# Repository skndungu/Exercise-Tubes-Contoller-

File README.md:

# Exercise-Tubes-Contoller
Controller for exercise tubes 

# Exercise Tubes Contoller 3 Speed Levels

Test codes for solenoids driven via io expander and the arduino

The Code is used to test the PCB board and connections with the solenoids, it put on/off the solenoids at intervals of one sec

PCF8574 GPIO Extender
---
i2c addresses, the table below is used to assign the addresses

Programming
---
- Download the codes from the codes from the ⬇️ on the code section, you will get a folder with the name 📁 `Exercise-Tubes-Contoller--master`
- Extract the content of the zipped file, you will get the firmware codes and another folder with the name 📁 `libs` extract the content from the folder and paste it on your 📂 `documents/Arduino/library/` directory to add the lib used in this case
- Compile and run codes
- Upload to the dev board and test out your codes!

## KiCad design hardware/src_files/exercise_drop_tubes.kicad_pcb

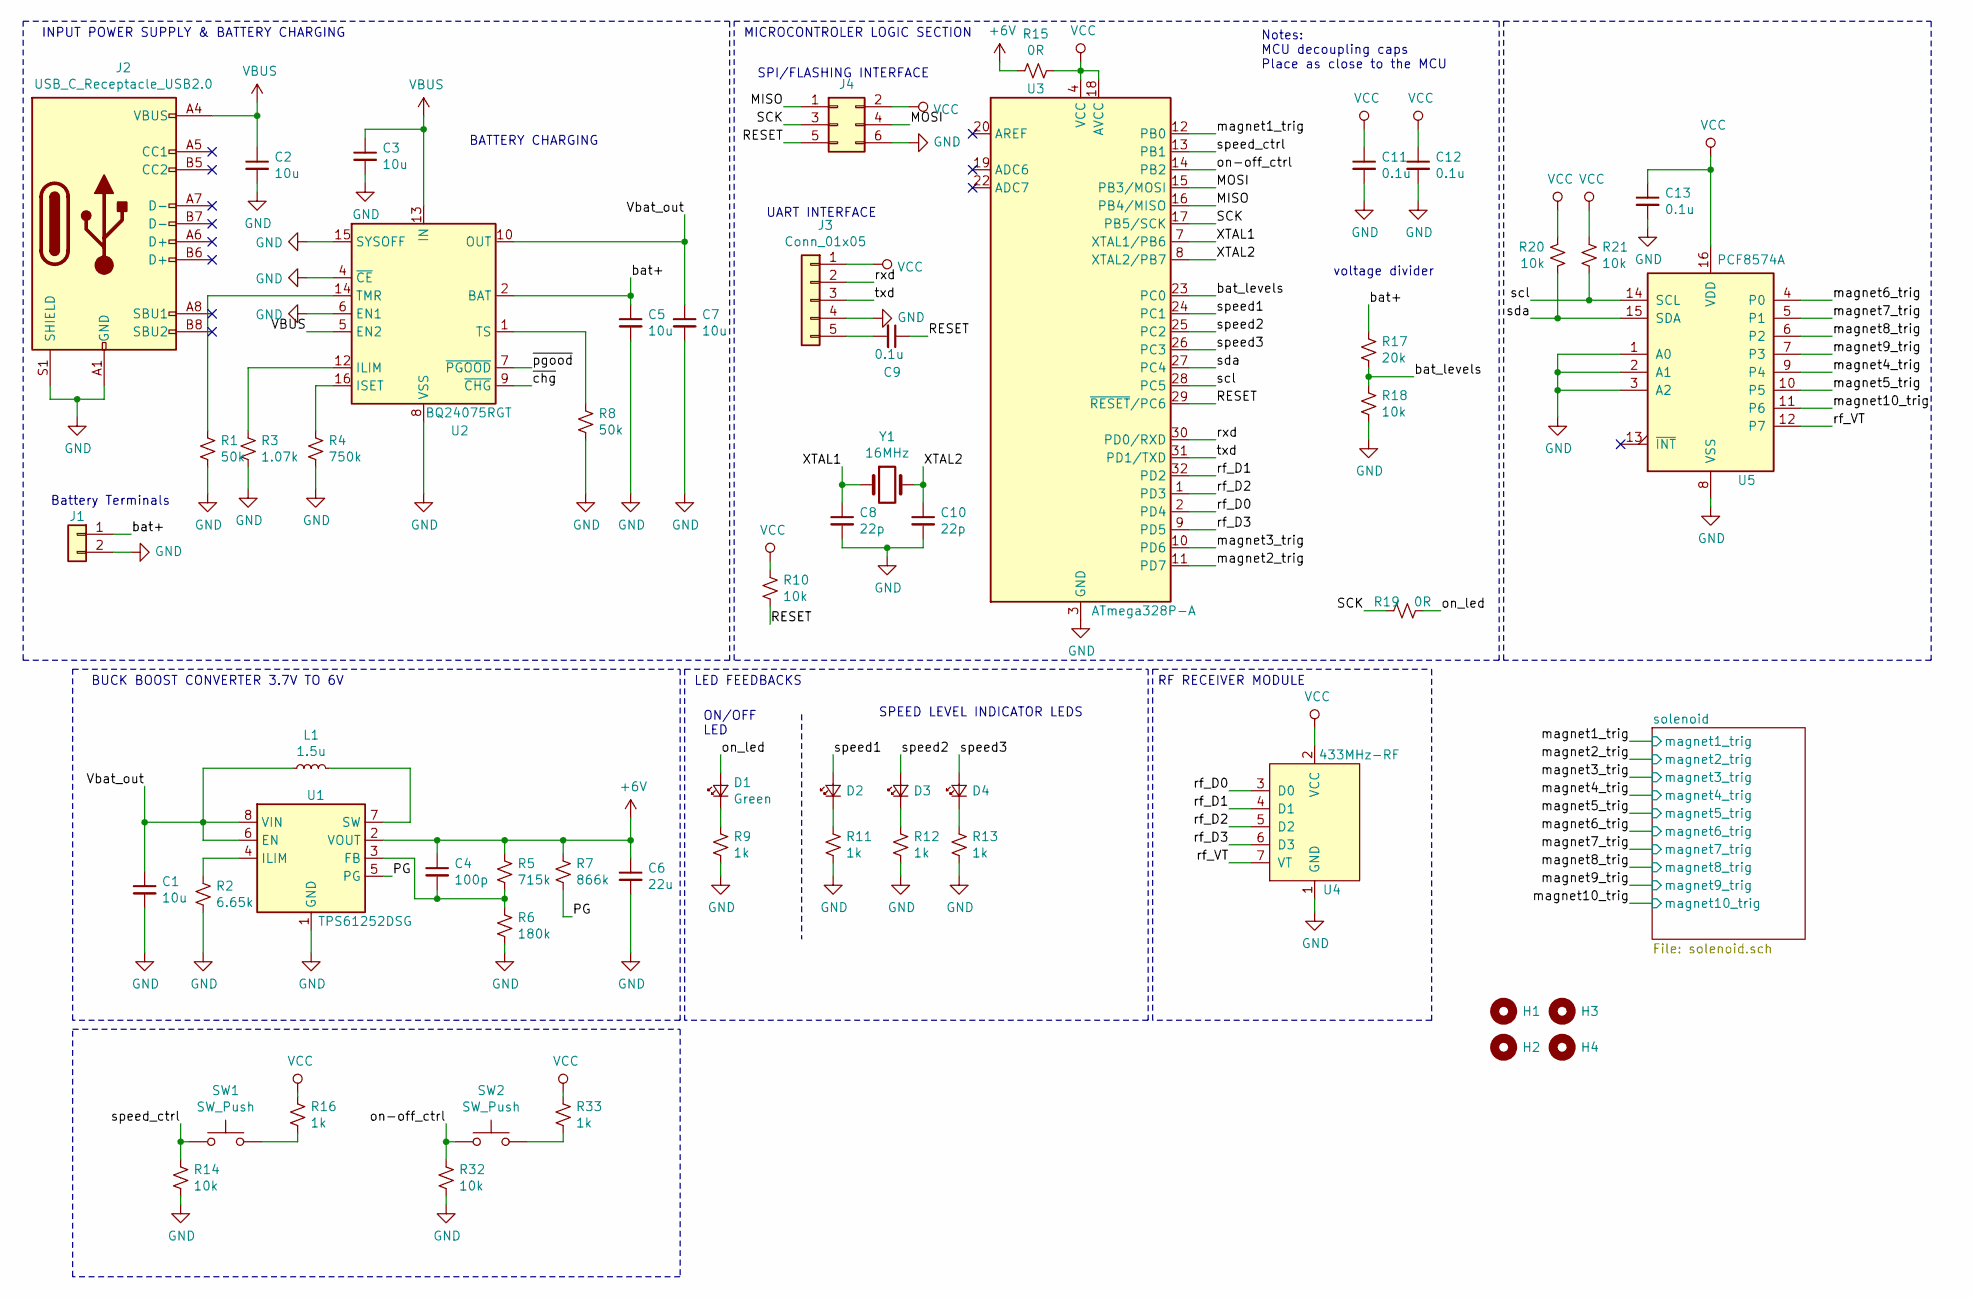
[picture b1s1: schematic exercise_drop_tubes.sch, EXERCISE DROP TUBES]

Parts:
C1, C2, C3, C5, C7: 10u; C_0603_1608Metric
C4: 100p; C_0603_1608Metric
C6: 22u; C_0603_1608Metric
C8, C10: 22p; C_0603_1608Metric
C9, C11, C12, C13: 0.1u; C_0603_1608Metric
D1: Green; LED_Rectangular_W3.0mm_H2.0mm
D2, D3, D4: LED_Small; LED_Rectangular_W3.0mm_H2.0mm
H1, H2, H3, H4: MountingHole; MountingHole_3.2mm_M3
J1: Conn_01x02; JST_XH_S2B-XH-A_1x02_P2.50mm_Horizontal
J2: USB_C_Receptacle_USB2.0; USB_C_Receptacle_Amphenol_12401548E4-2A
J3: Conn_01x05; PinHeader_1x05_P2.54mm_Vertical
J4: Conn_02x03_Odd_Even; PinHeader_2x03_P2.54mm_Vertical
L1: 1.5u; YSPI1050-xxx
R1, R8: 50k; R_0603_1608Metric
R2: 6.65k; R_0603_1608Metric
R3: 1.07k; R_0603_1608Metric
R4: 750k; R_0603_1608Metric
R5: 715k; R_0603_1608Metric
R6: 180k; R_0603_1608Metric
R7: 866k; R_0603_1608Metric
R9, R11, R12, R13, R16, R33: 1k; R_0603_1608Metric
R10, R14, R18, R20, R21, R32: 10k; R_0603_1608Metric
R15, R19: 0R; R_0603_1608Metric
R17: 20k; R_0603_1608Metric
SW1, SW2: SW_Push; UK-B0206-G8-160
U1: TPS61252DSG; WSON-8-1EP_2x2mm_P0.5mm_EP0.9x1.6mm
U2: BQ24075RGT; VQFN-16-1EP_3x3mm_P0.5mm_EP1.68x1.68mm_ThermalVias
U3: ATmega328P-A; TQFP-32_7x7mm_P0.8mm
U4: 433MHz-RF; RF-RX-433; Mfr# RX480E-4
U5: PCF8574A; SOIC-16W_7.5x10.3mm_P1.27mm
Y1: 16MHz; Crystal_SMD_Abracon_ABM8G-4Pin_3.2x2.5mm

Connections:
+6V: C4.1, C6.1, R5.1, R7.1, R15.2, U1.2 (VOUT); also elsewhere on the board
/MISO: J4.1, U3.16 (PB4/MISO)
/MOSI: J4.4, U3.15 (PB3/MOSI)
/PG: R7.2, U1.5 (PG)
/RESET: C9.1, J4.5, R10.1, U3.29 (~RESET~/PC6)
/SCK: J4.3, R19.2, U3.17 (PB5/SCK)
/Vbat_out: C1.1, C7.1, L1.1, U1.6 (EN), U1.8 (VIN), U2.10 (OUT), U2.11 (OUT)
/XTAL1: C8.1, U3.7 (XTAL1/PB6), Y1.1
/XTAL2: C10.1, U3.8 (XTAL2/PB7), Y1.3
/bat+: C5.1, J1.1, R17.1, U2.2 (BAT), U2.3 (BAT)
/bat_levels: R17.2, R18.1, U3.23 (PC0)
/magnet1_trig: U3.12 (PB0); also elsewhere on the board
/magnet2_trig: U3.11 (PD7); also elsewhere on the board
/magnet3_trig: U3.10 (PD6); also elsewhere on the board
/magnet4_trig: U5.9 (P4); also elsewhere on the board
/magnet5_trig: U5.10 (P5); also elsewhere on the board
/magnet6_trig: U5.4 (P0); also elsewhere on the board
/magnet7_trig: U5.5 (P1); also elsewhere on the board
/magnet8_trig: U5.6 (P2); also elsewhere on the board
/magnet9_trig: U5.7 (P3); also elsewhere on the board
/magnet10_trig: U5.11 (P6); also elsewhere on the board
/on-off_ctrl: R32.1, SW2.1, U3.14 (PB2)
/on_led: D1.2 (A), R19.1
/rf_D0: U3.2 (PD4), U4.3 (D0)
/rf_D1: U3.32 (PD2), U4.4 (D1)
/rf_D2: U3.1 (PD3), U4.5 (D2)
/rf_D3: U3.9 (PD5), U4.6 (D3)
/rf_VT: U4.7 (VT), U5.12 (P7)
/rxd: J3.2, U3.30 (PD0/RXD)
/scl: R21.2, U3.28 (PC5), U5.14 (SCL)
/sda: R20.2, U3.27 (PC4), U5.15 (SDA)
/speed1: D2.2 (A), U3.24 (PC1)
/speed2: D3.2 (A), U3.25 (PC2)
/speed3: D4.2 (A), U3.26 (PC3)
/speed_ctrl: R14.1, SW1.1, U3.13 (PB1)
/txd: J3.3, U3.31 (PD1/TXD)
GND: C1.2, C2.2, C3.2, C5.2, C6.2, C7.2, C8.2, C10.2, C11.2, C12.2, C13.2, J1.2, J2.A1 (GND), J2.A12 (GND), J2.B1 (GND), J2.B12 (GND), J2.S1 (SHIELD), J3.4, J4.6, R1.2, R2.2, R3.2, R4.2, R6.2, R8.2, R9.2, R11.2, R12.2, R13.2, R14.2, R18.2, R32.2, U1.1 (GND), U1.9 (GND), U2.4 (~CE), U2.6 (EN1), U2.8 (VSS), U2.15 (SYSOFF), U2.17 (VSS), U3.3 (GND), U3.5 (GND), U3.21 (GND), U4.1 (GND), U5.1 (A0), U5.2 (A1), U5.3 (A2), U5.8 (VSS); also elsewhere on the board
unnamed: C4.2, R5.2, R6.1, U1.3 (FB)
unnamed: C9.2, J3.5
unnamed: D1.1 (K), R9.1
unnamed: D2.1 (K), R11.1
unnamed: D3.1 (K), R12.1
unnamed: D4.1 (K), R13.1
unnamed: L1.2, U1.7 (SW)
unnamed: R1.1, U2.14 (TMR)
unnamed: R2.1, U1.4 (ILIM)
unnamed: R3.1, U2.12 (ILIM)
unnamed: R4.1, U2.16 (ISET)
unnamed: R8.1, U2.1 (TS)
unnamed: R16.2, SW1.3
unnamed: R33.2, SW2.3
VBUS: C2.1, C3.1, J2.A4 (VBUS), J2.A9 (VBUS), J2.B4 (VBUS), J2.B9 (VBUS), U2.5 (EN2), U2.13 (IN)
VCC: C11.1, C12.1, C13.1, J3.1, J4.2, R10.2, R15.1, R16.1, R20.1, R21.1, R33.1, U3.4 (VCC), U3.6 (VCC), U3.18 (AVCC), U4.2 (VCC), U5.16 (VDD)

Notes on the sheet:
Notes: MCU decoupling caps Place as close to the MCU
Battery Terminals
voltage divider
INPUT POWER SUPPLY & BATTERY CHARGING
BUCK BOOST CONVERTER 3.7V TO 6V
MICROCONTROLER LOGIC SECTION
UART INTERFACE
SPI/FLASHING INTERFACE
BATTERY CHARGING
ON/OFF LED
SPEED LEVEL INDICATOR LEDS
LED FEEDBACKS
RF RECEIVER MODULE

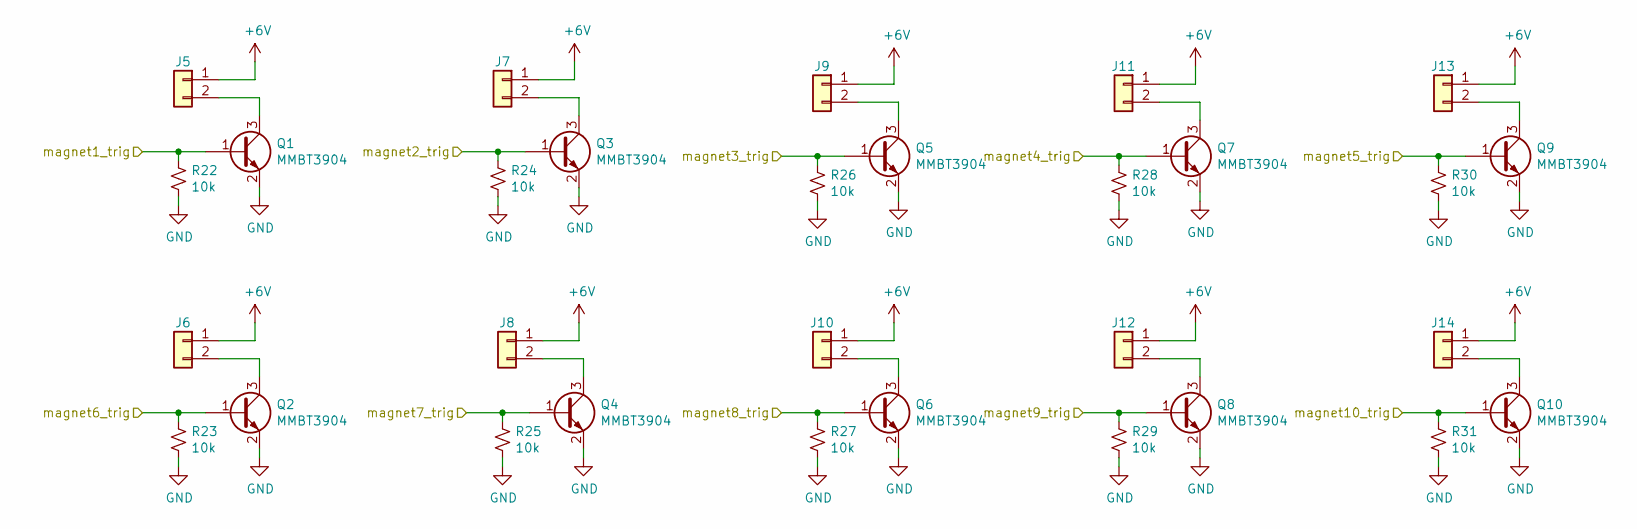
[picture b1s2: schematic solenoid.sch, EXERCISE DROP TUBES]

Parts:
J5, J6, J7, J8, J9, J10, J11, J12, J13, J14: Conn_01x02; JST_XH_S2B-XH-A_1x02_P2.50mm_Horizontal
Q1, Q2, Q3, Q4, Q5, Q6, Q7, Q8, Q9, Q10: MMBT3904; SOT-23
R22, R23, R24, R25, R26, R27, R28, R29, R30, R31: 10k; R_0603_1608Metric

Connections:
+6V: J5.1, J6.1, J7.1, J8.1, J9.1, J10.1, J11.1, J12.1, J13.1, J14.1; also elsewhere on the board
/magnet1_trig: Q1.1 (B), R22.1; also elsewhere on the board
/magnet2_trig: Q3.1 (B), R24.1; also elsewhere on the board
/magnet3_trig: Q5.1 (B), R26.1; also elsewhere on the board
/magnet4_trig: Q7.1 (B), R28.1; also elsewhere on the board
/magnet5_trig: Q9.1 (B), R30.1; also elsewhere on the board
/magnet6_trig: Q2.1 (B), R23.1; also elsewhere on the board
/magnet7_trig: Q4.1 (B), R25.1; also elsewhere on the board
/magnet8_trig: Q6.1 (B), R27.1; also elsewhere on the board
/magnet9_trig: Q8.1 (B), R29.1; also elsewhere on the board
/magnet10_trig: Q10.1 (B), R31.1; also elsewhere on the board
GND: Q1.2 (E), Q2.2 (E), Q3.2 (E), Q4.2 (E), Q5.2 (E), Q6.2 (E), Q7.2 (E), Q8.2 (E), Q9.2 (E), Q10.2 (E), R22.2, R23.2, R24.2, R25.2, R26.2, R27.2, R28.2, R29.2, R30.2, R31.2; also elsewhere on the board
unnamed: J5.2, Q1.3 (C)
unnamed: J6.2, Q2.3 (C)
unnamed: J7.2, Q3.3 (C)
unnamed: J8.2, Q4.3 (C)
unnamed: J9.2, Q5.3 (C)
unnamed: J10.2, Q6.3 (C)
unnamed: J11.2, Q7.3 (C)
unnamed: J12.2, Q8.3 (C)
unnamed: J13.2, Q9.3 (C)
unnamed: J14.2, Q10.3 (C)

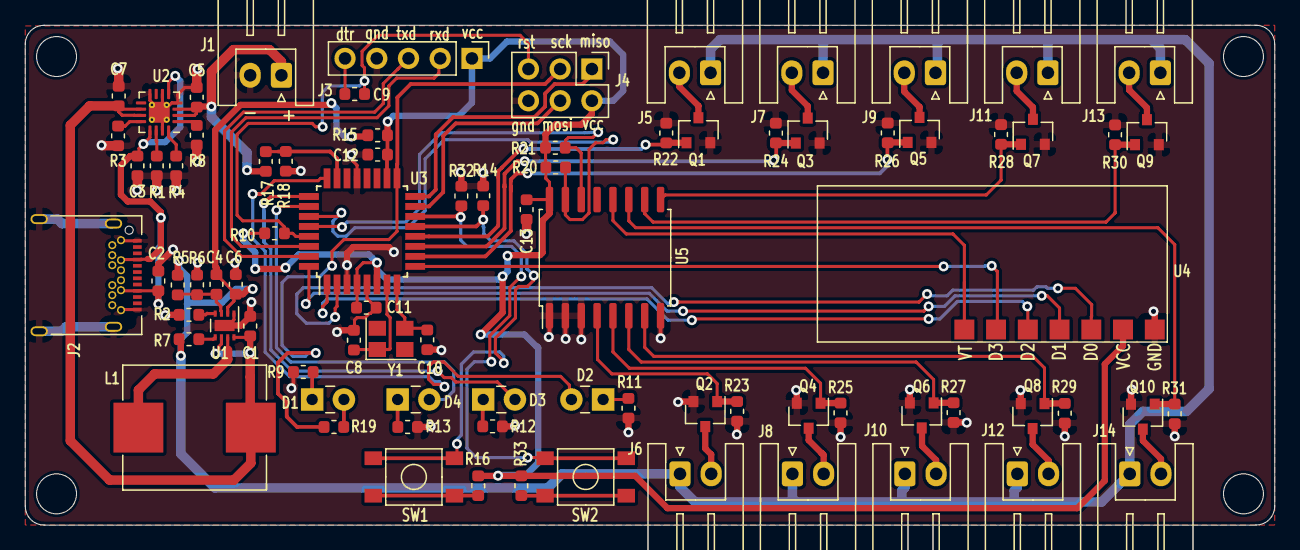
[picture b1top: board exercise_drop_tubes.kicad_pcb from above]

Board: 2 copper layers, 100.0 x 40.0 mm, 87 parts (0 on the bottom side), 63 nets.

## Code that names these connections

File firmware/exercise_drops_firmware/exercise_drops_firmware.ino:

/*
* Title: Exercise Drop Tubes 
*
* Author: Simon Ndungu
*
* Date: 21st Nov 2021
*/
#include "Arduino.h"
#include "PCF8574.h"

/* U5 --> A0,A1,A2 = 0 => address => 0x20 */
/* Set i2c address */ 
// create an object of the PCF8574 
PCF8574 pcf8574_U1(0x20);

#define solenoid1_trig 8
#define solenoid2_trig 7
#define solenoid3_trig 6

#define speed_ctrl_btn 9
#define on_off_ctrl_btn 10

#define bat_level A0

#define speed1_led A1
#define speed2_led A2
#define speed3_led A3
#define status_led 13

#define rf_d0 2
#define rf_d1 3
#define rf_d2 4
#define rf_d3 5

float R1 = 20000;
float R2 = 10000;
float voltage_raw_val = 0.00;
float voltage_out = 0.00;
float battery_voltage = 0.00;
float correction_factor = 0.13;

int random_tube;
int previous_random_tube;
int speed_ctrl_btn_state = 0;
int on_off_ctrl_btn_state = 0;


unsigned long currentMillis=0;
unsigned long previousMillis = 0;
int speed1 = 1000; // value can be changed by buttons
int speed2 = 2000;
int speed3 = 3000; 
int interval; 

bool level1_speed = true;
bool level2_speed = false;
bool level3_speed = false;

int count = 0;



void setup() {
  // put your setup code here, to run once:
	  pcf8574_U1.pinMode(P0, OUTPUT); // solenoid 6
      pcf8574_U1.pinMode(P1, OUTPUT); // solenoid 7
      pcf8574_U1.pinMode(P2, OUTPUT); // solenoid 8
      pcf8574_U1.pinMode(P3, OUTPUT); // solenoid 4
      pcf8574_U1.pinMode(P5, OUTPUT); // solenoid 5
      pcf8574_U1.pinMode(P6, OUTPUT); // solenoid 10
      pcf8574_U1.pinMode(P7, OUTPUT); // RF VT signal

      pinMode(solenoid1_trig, OUTPUT);
      pinMode(solenoid2_trig, OUTPUT);
      pinMode(solenoid3_trig, OUTPUT);

      pinMode(speed1_led, OUTPUT);
      pinMode(speed2_led, OUTPUT);
      pinMode(speed3_led, OUTPUT);
      pinMode(status_led, OUTPUT);

      pinMode(speed_ctrl_btn, INPUT);
      pinMode(on_off_ctrl_btn, INPUT);
      pinMode(bat_level, INPUT);

}

void loop() {
  // put your main code here, to run repeatedly:
   unsigned long currentMillis = millis();

   execute_speed_change();
   
   generate_random_tube(); // executes the tubes

}

void take_reading(){
  voltage_raw_val = analogRead(bat_level);
  speed_ctrl_btn_state = digitalRead(speed_ctrl_btn);
  on_off_ctrl_btn_state = digitalRead(on_off_ctrl_btn);

  Serial.print("Raw Value");
  Serial.println(voltage_raw_val);
}

void check_battery_voltage(){
  take_reading();
  voltage_out = (voltage_raw_val * 5) / 1024; 
  battery_voltage = voltage_out / (R2/(R1+ R2)) - correction_factor;
  Serial.print("Measured Voltage is: ");
  Serial.print(battery_voltage);
  Serial.println("V");
  }


void speed1_led_on(){
   digitalWrite(speed1_led, HIGH);
}
void speed1_led_off(){
  digitalWrite(speed1_led, LOW);
}
void speed2_led_on(){
  digitalWrite(speed2_led, HIGH);
}
void speed2_led_off(){
  digitalWrite(speed2_led, LOW);
}
void speed3_led_on(){
  digitalWrite(speed3_led, HIGH);
}
void speed3_led_off(){
  digitalWrite(speed3_led, LOW);
}

int generate_random_tube(){
   if ((unsigned long )(currentMillis - previousMillis) >= interval) {
      random_tube = random(11);
      Serial.print("Random Number");
      Serial.println(random_tube);
      previousMillis = currentMillis;
      previous_random_tube = random_tube;
   }

   return random_tube;
   trigger_solenoids();
}

void listen_change_speed(){
   if(speed_ctrl_btn_state == 1){
      count +=1;
   }

   if(count == 1){
   	 level1_speed = true;
     level2_speed = false;
     level3_speed = false;
   }

   if(count == 2){
     level1_speed = false;
     level2_speed = true;
     level3_speed = false;
   }

   if(count == 3){
     level1_speed = false;
     level2_speed = false;
     level3_speed = true;
   }

   if(count > 3){
    count = 1; //resets count to 1 if val > 3(reps speed levels)
   }
   
}

void execute_speed_change(){
  listen_change_speed();
  if(level1_speed){
    speed1_led_on();
    speed2_led_off();
    speed3_led_off();
    interval = speed3; // level 1 is the slowest speed 
  }
    if(level2_speed){
    speed1_led_off();
    speed2_led_on();
    speed3_led_off();
    interval = speed2; // level 2 is the medium speed 
  }
    if(level3_speed){
    speed1_led_off();
    speed2_led_off();
    speed3_led_on();
    interval = speed1; // level 1 is the fastest speed 
  }
}

void trigger_solenoids(){
 int tube = generate_random_tube();
 Serial.print("Random Tube Passed is: ");
 Serial.println(tube);
 if(tube == 1){
   digitalWrite(solenoid1_trig, HIGH);
   digitalWrite(solenoid2_trig, LOW);
   digitalWrite(solenoid3_trig, LOW);
   pcf8574_U1.digitalWrite(P0, LOW);
   pcf8574_U1.digitalWrite(P1, LOW);
   pcf8574_U1.digitalWrite(P2, LOW);
   pcf8574_U1.digitalWrite(P3, LOW);
   pcf8574_U1.digitalWrite(P4, LOW);
   pcf8574_U1.digitalWrite(P5, LOW);
   pcf8574_U1.digitalWrite(P6, LOW);
 }
  if(tube == 2){
   digitalWrite(solenoid1_trig, LOW);
   digitalWrite(solenoid2_trig, HIGH);
   digitalWrite(solenoid3_trig, LOW);
   pcf8574_U1.digitalWrite(P0, LOW);
   pcf8574_U1.digitalWrite(P1, LOW);
   pcf8574_U1.digitalWrite(P2, LOW);
   pcf8574_U1.digitalWrite(P3, LOW);
   pcf8574_U1.digitalWrite(P4, LOW);
   pcf8574_U1.digitalWrite(P5, LOW);
   pcf8574_U1.digitalWrite(P6, LOW);
 }
  if(tube == 3){
   digitalWrite(solenoid1_trig, LOW);
   digitalWrite(solenoid2_trig, LOW);
   digitalWrite(solenoid3_trig, HIGH);
   pcf8574_U1.digitalWrite(P0, LOW);
   pcf8574_U1.digitalWrite(P1, LOW);
   pcf8574_U1.digitalWrite(P2, LOW);
   pcf8574_U1.digitalWrite(P3, LOW);
   pcf8574_U1.digitalWrite(P4, LOW);
   pcf8574_U1.digitalWrite(P5, LOW);
   pcf8574_U1.digitalWrite(P6, LOW);
 }
  if(tube == 4){
   digitalWrite(solenoid1_trig, LOW);
   digitalWrite(solenoid2_trig, LOW);
   digitalWrite(solenoid3_trig, LOW);
   pcf8574_U1.digitalWrite(P0, HIGH);
   pcf8574_U1.digitalWrite(P1, LOW);
   pcf8574_U1.digitalWrite(P2, LOW);
   pcf8574_U1.digitalWrite(P3, LOW);
   pcf8574_U1.digitalWrite(P4, LOW);
   pcf8574_U1.digitalWrite(P5, LOW);
   pcf8574_U1.digitalWrite(P6, LOW);
 }
  if(tube == 5){
   digitalWrite(solenoid1_trig, LOW);
   digitalWrite(solenoid2_trig, LOW);
   digitalWrite(solenoid3_trig, LOW);
   pcf8574_U1.digitalWrite(P0, LOW);
   pcf8574_U1.digitalWrite(P1, HIGH);
   pcf8574_U1.digitalWrite(P2, LOW);
   pcf8574_U1.digitalWrite(P3, LOW);
   pcf8574_U1.digitalWrite(P4, LOW);
   pcf8574_U1.digitalWrite(P5, LOW);
   pcf8574_U1.digitalWrite(P6, LOW);
 }
  if(tube == 6){
   digitalWrite(solenoid1_trig, LOW);
   digitalWrite(solenoid2_trig, LOW);
   digitalWrite(solenoid3_trig, LOW);
   pcf8574_U1.digitalWrite(P0, LOW);
   pcf8574_U1.digitalWrite(P1, LOW);
   pcf8574_U1.digitalWrite(P2, HIGH);
   pcf8574_U1.digitalWrite(P3, LOW);
   pcf8574_U1.digitalWrite(P4, LOW);
   pcf8574_U1.digitalWrite(P5, LOW);
   pcf8574_U1.digitalWrite(P6, LOW);
 }
  if(tube == 7){
   digitalWrite(solenoid1_trig, LOW);
   digitalWrite(solenoid2_trig, LOW);
   digitalWrite(solenoid3_trig, LOW);
   pcf8574_U1.digitalWrite(P0, LOW);
   pcf8574_U1.digitalWrite(P1, LOW);
   pcf8574_U1.digitalWrite(P2, LOW);
   pcf8574_U1.digitalWrite(P3, HIGH);
   pcf8574_U1.digitalWrite(P4, LOW);
   pcf8574_U1.digitalWrite(P5, LOW);
   pcf8574_U1.digitalWrite(P6, LOW);
 }
  if(tube == 8){
   digitalWrite(solenoid1_trig, LOW);
   digitalWrite(solenoid2_trig, LOW);
   digitalWrite(solenoid3_trig, LOW);
   pcf8574_U1.digitalWrite(P0, LOW);
   pcf8574_U1.digitalWrite(P1, LOW);
   pcf8574_U1.digitalWrite(P2, LOW);
   pcf8574_U1.digitalWrite(P3, LOW);
   pcf8574_U1.digitalWrite(P4, HIGH);
   pcf8574_U1.digitalWrite(P5, LOW);
   pcf8574_U1.digitalWrite(P6, LOW);
 }
  if(tube == 9){
   digitalWrite(solenoid1_trig, LOW);
   digitalWrite(solenoid2_trig, LOW);
   digitalWrite(solenoid3_trig, LOW);
   pcf8574_U1.digitalWrite(P0, LOW);
   pcf8574_U1.digitalWrite(P1, LOW);
   pcf8574_U1.digitalWrite(P2, LOW);
   pcf8574_U1.digitalWrite(P3, LOW);
   pcf8574_U1.digitalWrite(P4, LOW);
   pcf8574_U1.digitalWrite(P5, HIGH);
   pcf8574_U1.digitalWrite(P6, LOW);
 }
  if(tube == 10){
   digitalWrite(solenoid1_trig, LOW);
   digitalWrite(solenoid2_trig, LOW);
   digitalWrite(solenoid3_trig, LOW);
   pcf8574_U1.digitalWrite(P0, LOW);
   pcf8574_U1.digitalWrite(P1, LOW);
   pcf8574_U1.digitalWrite(P2, LOW);
   pcf8574_U1.digitalWrite(P3, LOW);
   pcf8574_U1.digitalWrite(P4, LOW);
   pcf8574_U1.digitalWrite(P5, LOW);
   pcf8574_U1.digitalWrite(P6, HIGH);
 }
 
}

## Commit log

2021-11-23 firmware files comitted
    firmware files comitted
2021-11-23 All hardware files commit
    hardware files commit
